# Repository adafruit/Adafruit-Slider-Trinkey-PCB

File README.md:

## Adafruit Slider Trinkey PCB

<a href="http://www.adafruit.com/products/5021"><br/>
Click here to purchase one from the Adafruit shop</a>

PCB files for the Adafruit Slider Trinkey. 

Format is EagleCAD schematic and board layout
* https://www.adafruit.com/product/5021

### Description

It's half USB Key, half Adafruit Trinket, half mini slide pot... it's Slider Trinkey, the circuit board with a Trinket M0 heart, NeoPixel glow, and a 35mm long 10KΩ slide potentiometer.

The PCB is designed to slip into any USB A port on a computer or laptop. There's an ATSAMD21 microcontroller on board with just enough circuitry to keep it happy. One pin of the microcontroller connects to the middle of the slide potentiometer as an analog input. Another connects to two NeoPixel LEDs. The third pin can be used as a capacitive touch input. A reset button lets you enter bootloader mode if necessary. That's it!

The SAMD21 can run CircuitPython or Arduino very nicely - with existing NeoPixel and our FreeTouch libraries for the capacitive touch input. Over the USB connection, you can have serial, MIDI, or HID connectivity. The Slider Trinkey is perfect for simple projects that can use a few user inputs and colorful output. Maybe you'll set it up as a monitor brightness adjuster, or volume control, or color picker.

Please note this board DOES come with a pre-soldered slide pot (there's really only one that fits and we happen to stock it) Since we use a PCB with a USB A shape, its possible to accidentally yank the board out if you push the potentiometer all way, way out and then keep pushing out. So be kind and careful with your Slider Trinkey! It isn't meant for yanking.

We think it's just an adorable little board, small and durable and inexpensive enough that it could be a first microcontroller board, or inspiration for advanced developers to make something simple and fun.

* ATSAMD21E18 32-bit Cortex M0+ - 48 MHz 32 bit processor with 256KB Flash and 32 KB RAM
* Native USB supported by every OS - can be used in Arduino or CircuitPython as USB serial console, MIDI, Keyboard/Mouse HID, even a little disk drive for storing Python scripts.
* Can be used with Arduino IDE or CircuitPython
* Two reverse-mount RGB NeoPixel LEDs
* One Capacitive Touchpad
* One 35mm slide potentiometer with nubbin
* Reset switch for starting your project code over or entering bootloader mode
* Cute & keychain-friendly!

### License

Adafruit invests time and resources providing this open source design, please support Adafruit and open-source hardware by purchasing products from [Adafruit](https://www.adafruit.com)!

Designed by Limor Fried/Ladyada for Adafruit Industries.

Creative Commons Attribution/Share-Alike, all text above must be included in any redistribution. 
See license.txt for additional details.

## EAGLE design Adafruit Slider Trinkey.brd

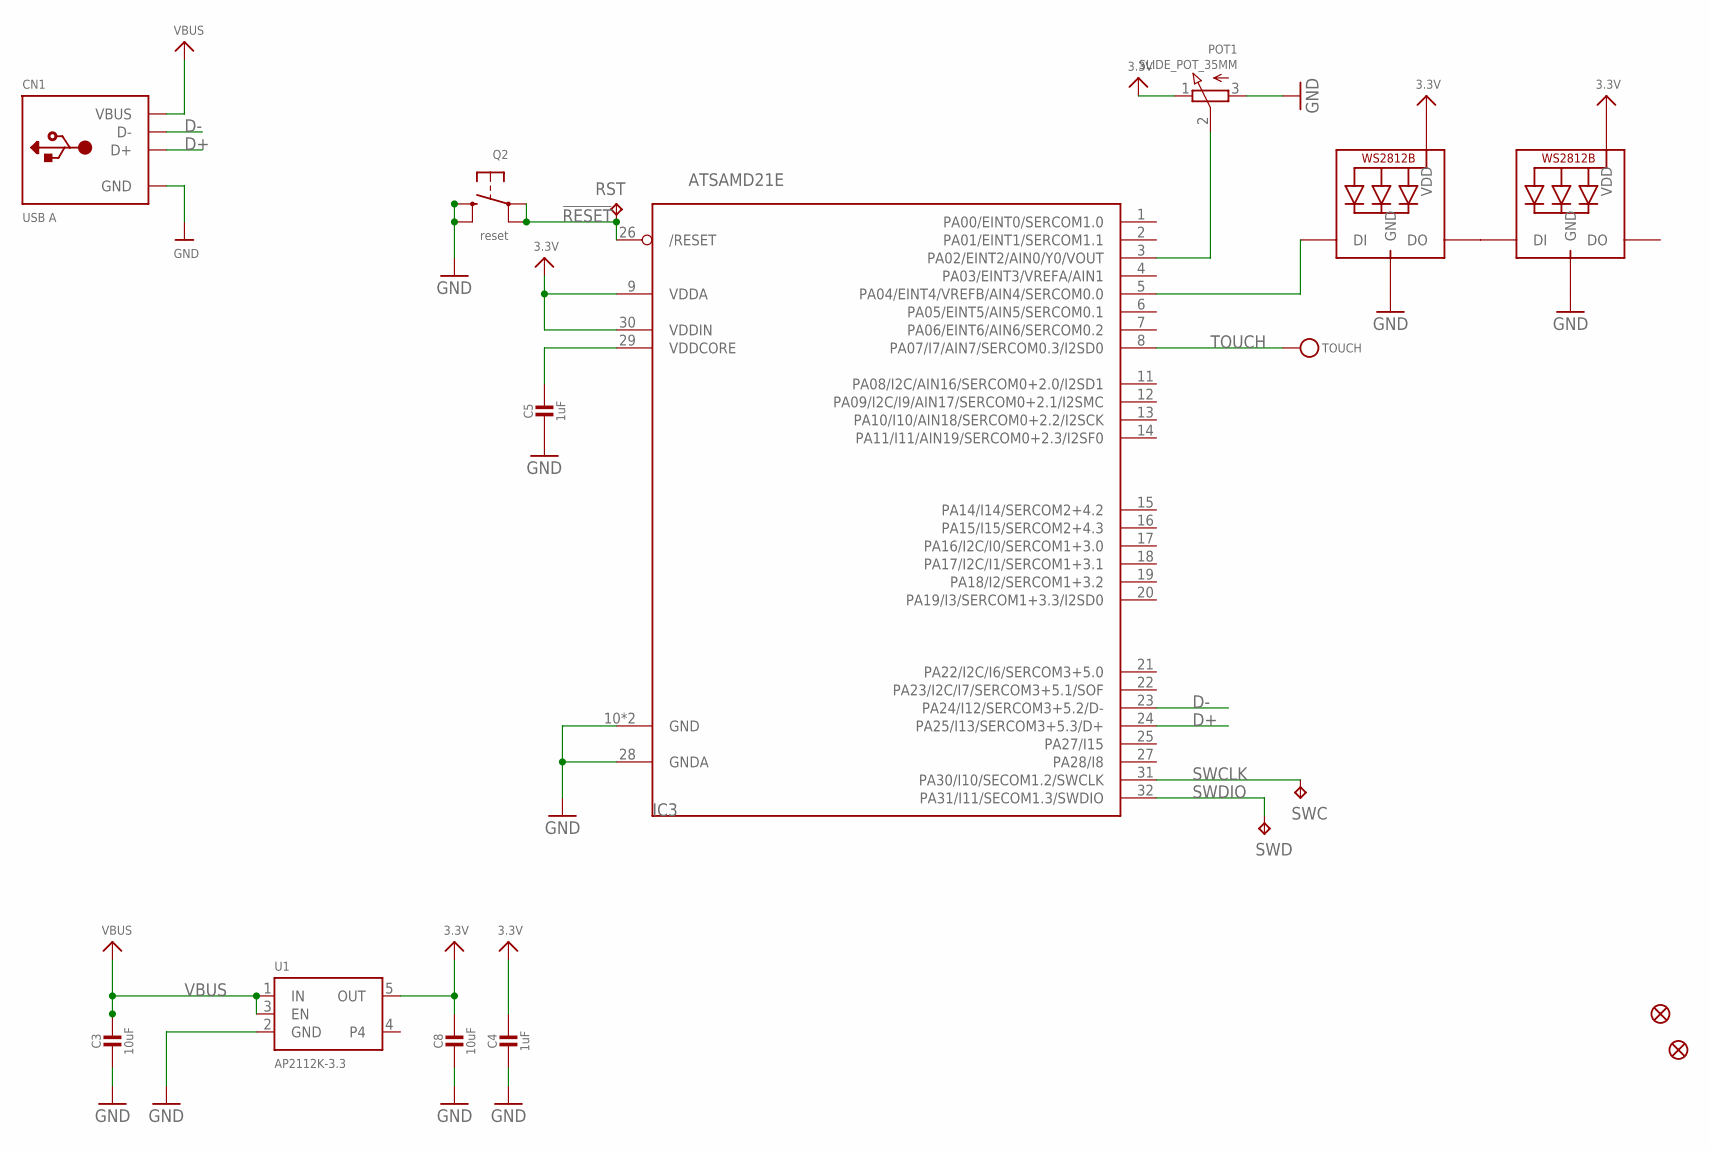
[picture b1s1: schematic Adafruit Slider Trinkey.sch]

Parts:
C3, C8: 10uF; 0805-NO
C4, C5: 1uF; 0603-NO
CN1: USB A; USBA_PCB
FID1, FID2: FIDUCIAL_1MM
IC3: ATSAMD21E; QFN32_5MM
LED1, LED2: WS2812B_SK6812E; NEO3535_REVERSE
POT1: SLIDE_POT_35MM
Q2: reset; BTN_KMR2_4.6X2.8
RST: TPTP16R; TP16R
SWC: TPTP15R; TP15R
SWD: TPTP16R; TP16R
TOUCH: TESTPOINTROUND0.5MM; TESTPOINT_ROUND_0.5MM
U1: AP2112K-3.3; SOT23-5

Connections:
3.3V: C4.1, C8.1, IC3.9 (VDDA), IC3.30 (VDDIN), LED1.1-VDD (VDD), LED2.1-VDD (VDD), POT1.1 (E), U1.5 (OUT)
!RESET: IC3.26 (/RESET), Q2.A, Q2.A' (P1), RST.TP
D+: CN1.USB_PLUS (D+), IC3.24 (PA25/I13/SERCOM3+5.3/D+)
D-: CN1.USB_NEG (D-), IC3.23 (PA24/I12/SERCOM3+5.2/D-)
GND: C3.2, C4.2, C5.2, C8.2, CN1.GND, IC3.10 (GND), IC3.28 (GNDA), IC3.33 (GND), LED1.3-GND (GND), LED2.3-GND (GND), POT1.3 (A), Q2.B (S), Q2.B' (S1), U1.2 (GND)
unnamed: IC3.5 (PA04/EINT4/VREFB/AIN4/SERCOM0.0), LED1.4-DIN (DI)
unnamed: LED1.2-DOUT (DO), LED2.4-DIN (DI)
POT: IC3.3 (PA02/EINT2/AIN0/Y0/VOUT), POT1.2 (S)
SWCLK: IC3.31 (PA30/I10/SECOM1.2/SWCLK), SWC.TP
SWDIO: IC3.32 (PA31/I11/SECOM1.3/SWDIO), SWD.TP
TOUCH: IC3.8 (PA07/I7/AIN7/SERCOM0.3/I2SD0), TOUCH.P$1
VBUS: C3.1, CN1.VCC (VBUS), U1.1 (IN), U1.3 (EN)
VDDCORE1: C5.1, IC3.29 (VDDCORE)

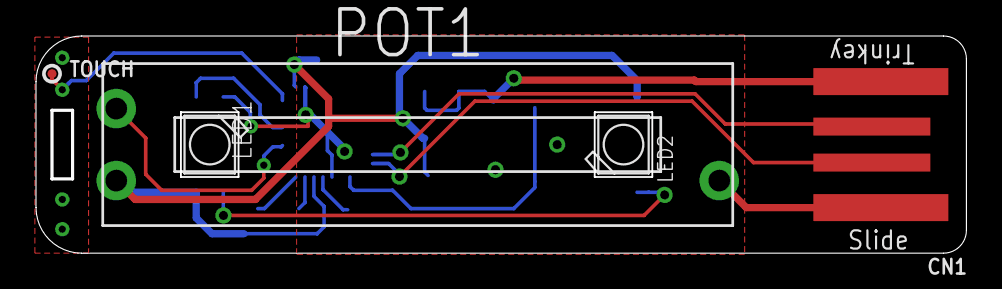
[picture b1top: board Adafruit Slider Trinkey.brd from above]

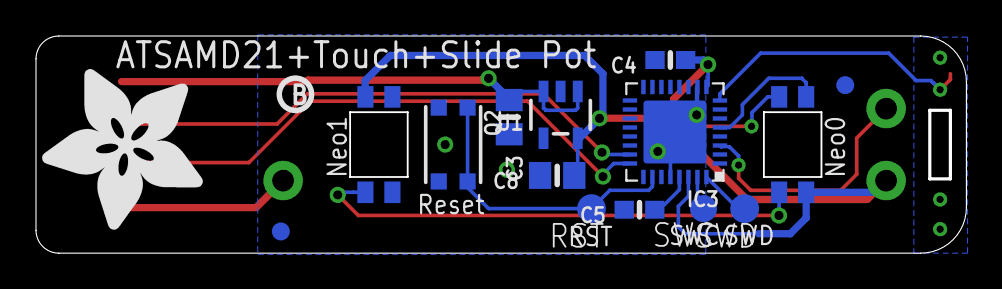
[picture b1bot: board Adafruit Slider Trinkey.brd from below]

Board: 2 copper layers, 51.5 x 11.9 mm, 19 parts (14 on the bottom side), 13 nets.

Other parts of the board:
U$6: ADAFRUIT_9MM
U$8: PCBFEAT-REV-040

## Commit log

2021-06-10 Adding board files.
2025-09-30 Delete Adafruit Slider Trinkey Pinout.pdf
    Replaced this with corrected version

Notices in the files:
parts and their libraries:
microbuilder: This work is placed in the public domain, and may be freely used for commercial and non-commercial work with the following conditions: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
